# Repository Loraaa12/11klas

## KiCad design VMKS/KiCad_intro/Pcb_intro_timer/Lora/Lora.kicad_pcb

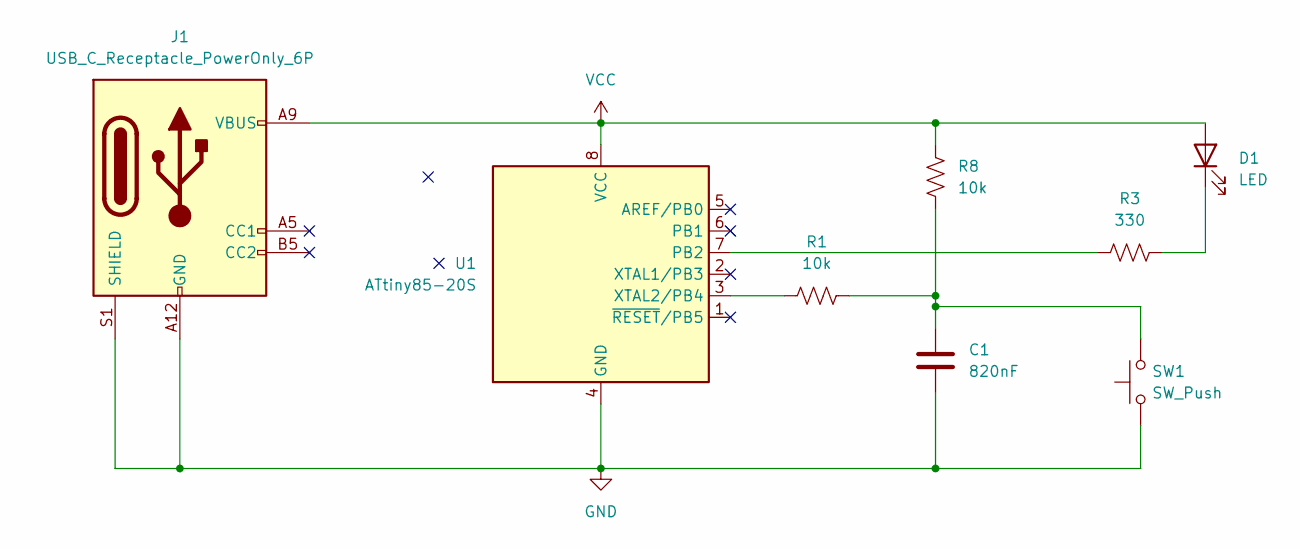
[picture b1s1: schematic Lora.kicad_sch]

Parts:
C1: 820nF; C_0805_2012Metric_Pad1.18x1.45mm_HandSolder
D1: LED; LED_0402_1005Metric
J1: USB_C_Receptacle_PowerOnly_6P; USB_C_Receptacle_HRO_TYPE-C-31-M-17
R1, R8: 10k; R_0402_1005Metric
R3: 330; R_1218_3246Metric
SW1: SW_Push; SW_Tactile_SPST_Angled_PTS645Vx31-2LFS
U1: ATtiny85-20S; SOIC-8W_5.3x5.3mm_P1.27mm

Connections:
GND: C1.2, J1.A12 (GND), J1.B12 (GND), J1.S1 (SHIELD), SW1.1, U1.4 (GND)
unnamed: C1.1, R1.2, R8.2, SW1.2
unnamed: D1.1 (K), R3.2
unnamed: R3.1, U1.7 (PB2)
unnamed: R1.1, U1.3 (XTAL2/PB4)
VCC: D1.2 (A), J1.A9 (VBUS), J1.B9 (VBUS), R8.1, U1.8 (VCC)

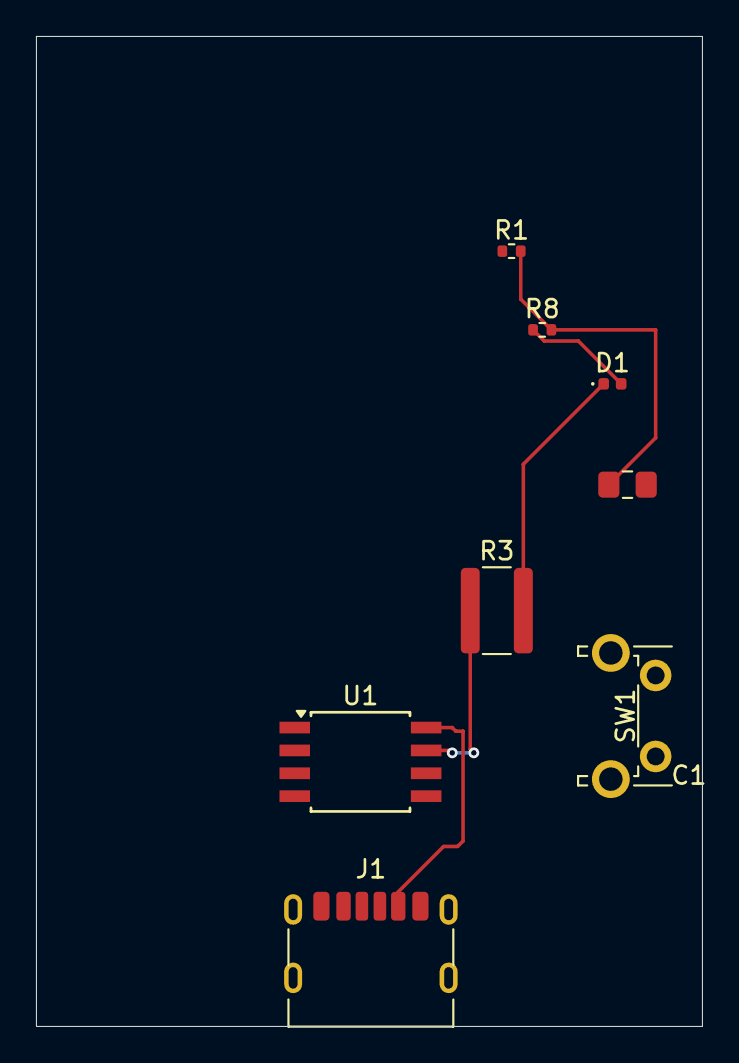
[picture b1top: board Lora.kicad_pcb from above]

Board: 2 copper layers, 37.0 x 55.0 mm, 8 parts (0 on the bottom side), 6 nets.

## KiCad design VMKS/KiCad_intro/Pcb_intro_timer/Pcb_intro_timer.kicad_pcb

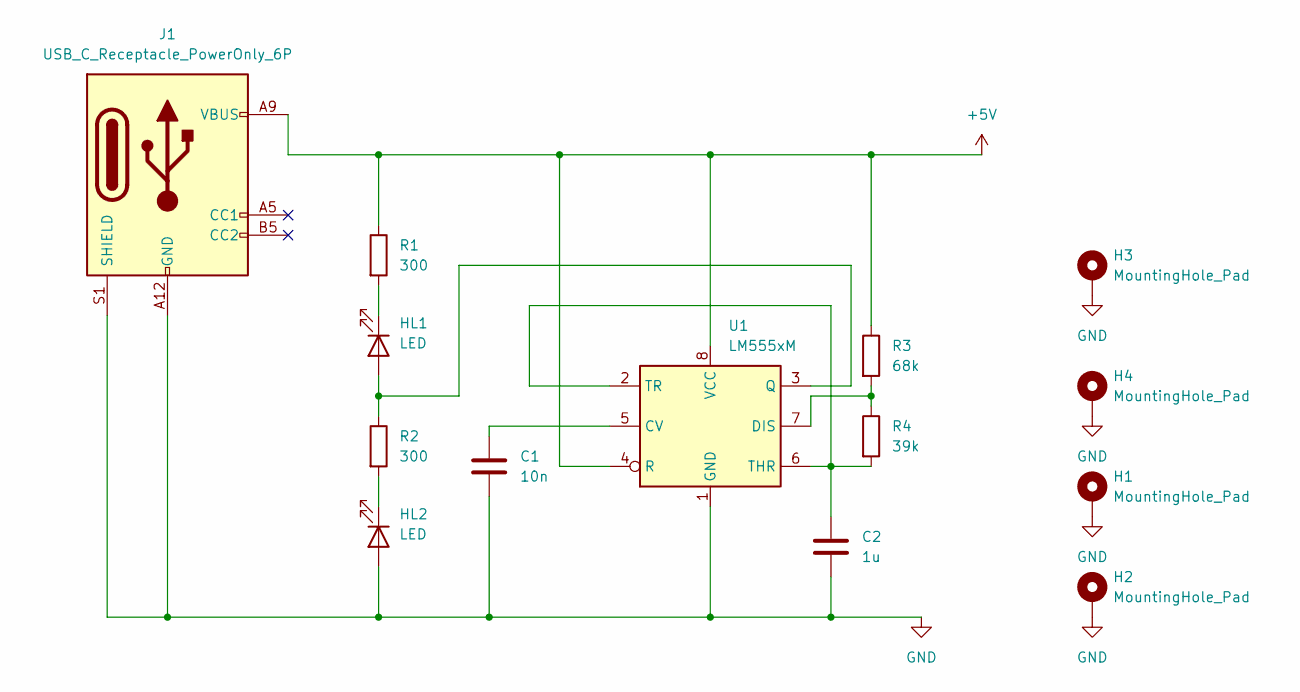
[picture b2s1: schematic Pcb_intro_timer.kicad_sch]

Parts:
C1: 10n; C_0805_2012Metric
C2: 1u; C_0805_2012Metric
H1, H2, H3, H4: MountingHole_Pad; MountingHole_3.5mm_Pad_Via
HL1, HL2: LED; LED_0805_2012Metric
J1: USB_C_Receptacle_PowerOnly_6P; USB_C_Receptacle_GCT_USB4135-GF-A_6P_TopMnt_Horizontal
R1, R2: 300; R_0805_2012Metric
R3: 68k; R_0805_2012Metric
R4: 39k; R_0805_2012Metric
U1: LM555xM; SOIC-8_3.9x4.9mm_P1.27mm

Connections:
+5V: J1.A9 (VBUS), J1.B9 (VBUS), R1.1, R3.1, U1.4 (R), U1.8 (VCC)
GND: C1.2, C2.2, H1.1, H2.1, H3.1, H4.1, HL2.2 (A), J1.A12 (GND), J1.B12 (GND), J1.S1 (SHIELD), U1.1 (GND)
unnamed: HL1.2 (A), R2.1, U1.3 (Q)
unnamed: HL1.1 (K), R1.2
unnamed: HL2.1 (K), R2.2
unnamed: C1.1, U1.5 (CV)
unnamed: R3.2, R4.1, U1.7 (DIS)
unnamed: C2.1, R4.2, U1.2 (TR), U1.6 (THR)

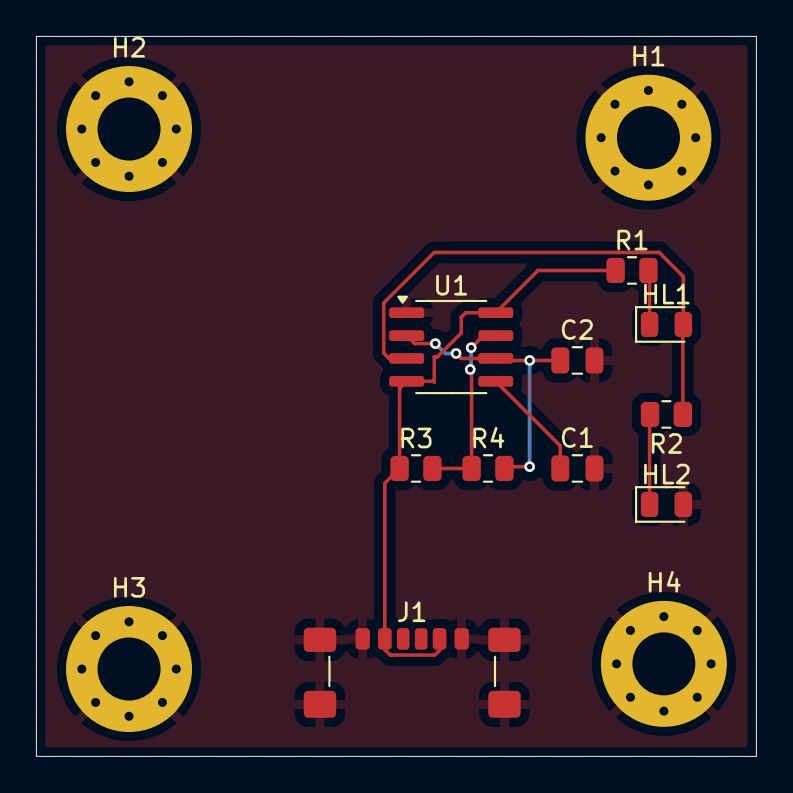
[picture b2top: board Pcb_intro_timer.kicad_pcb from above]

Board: 2 copper layers, 40.0 x 40.0 mm, 14 parts (0 on the bottom side), 8 nets.

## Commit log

2025-10-08 Create placeholder file
2025-10-08 Create placeholder
